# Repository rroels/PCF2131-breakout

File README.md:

# NXP PCF2131 RTC Breakout Board

> [!WARNING]
> The information and material (code, designs, files, ...) are provided "AS IS". We make no representation or warranty of any kind, express or implied, regarding the accuracy, adequacy, validity, reliability, availability, or completeness of any information or material. Use this at your own risk.

## Introduction

This repository contains a small breakout board for the NXP PCF2131 RTC.

The board has already been manufactured and tested, and I can confirm it works.

However, some design choices have been made that might not meet your needs. 
For instance, the board is wired for I2C communication only, and there is no support for battery switch-over.
Please read section "Design Considerations" for more info on the design choices.

For use with an Arduino, the [RTC NXP Arduino](https://reference.arduino.cc/reference/en/libraries/rtc_nxp_arduino/) library can be used to interface with the chip.

## Design Considerations

* Although the PCF2131 supports both I2C and SPI, they require different circuitry, and the choice was made to only support I2C.
* As expected for a I2C, pull-up resistors are present on the I2C lines.
* The board was not made to support battery switch-over, and for this reason, it does not have the suggested RC filter circuitry.

## Schematics

We base ourselves on the following recommended circuits from the datasheet:

I deliberately left out the RC filter for battery switch-over functionality, which led to the following schematics:

## Bill of Materials (BOM)

| Reference | Footprint                                   | Qty | Value      |
|-----------|---------------------------------------------|-----|------------|
| C1        | C_0603_1608Metric_Pad1.08x0.95mm_HandSolder | 1   | 1nF        |
| R3,R4     | R_0603_1608Metric_Pad0.98x0.95mm_HandSolder | 2   | 10k        |
| J1        | PinHeader_2x02_P2.54mm_Vertical             | 1   | Conn_01x04 |
| R2,R1     | R_0603_1608Metric_Pad0.98x0.95mm_HandSolder | 2   | 4.7k       |
| C2        | C_0603_1608Metric_Pad1.08x0.95mm_HandSolder | 1   | 100nF      |
| IC1       | SON50P350X450X150-17N-D                     | 1   | PCF2131TFY |
| J2        | PinHeader_1x07_P2.54mm_Horizontal           | 1   | Conn_01x07 |

See image of the PCB below to have a better idea of what these components look like. 

All capacitors and resistors and SMD 0603. Instead of the horizontal pin header I used, a vertical pin header will also work fine (as long as the pitch is 2.54mm).

## How to Obtain the Physical PCB

The Gerber file is in this repository (`gerber/PCF2131-breakout.zip`). Simply upload this file a PCB manufacturer of your choice (JLPCB, PCBWay, ...), and you they will make it for you for as low as \$5 for 5 pieces (with the cheapest shipping option, which can take a few weeks).

> [!WARNING]
> Note that you will still have to solder the components onto the PCB yourself!

## How to Edit Design

Everything you need to edit this design in KiCad 8 is included in the repository. 

However, this project uses symbols, footprints and 3D models from [Component Search Engine](https://componentsearchengine.com/). Their license allows us to do pretty much whatever we want with them, except redistributing them. For this reason I can't include them in this repository. 

If you would like to edit the design yourself, you will need to download the following component libraries from [https://componentsearchengine.com/](https://componentsearchengine.com/) (it's free!):

* [https://componentsearchengine.com/part-view/PCF2131TFY/NXP](https://componentsearchengine.com/part-view/PCF2131TFY/NXP)

From the downloaded zip file, move the content of the `KiCad` and `3D` subfolders into the project structure, so that the end-result looks like this:

The KiCad project is configured to look for these files in these locations, using relative paths, so no changes to the project itself are required. 

## Related Sources

* [https://www.nxp.com/products/analog-and-mixed-signal/real-time-clocks/nano-power-highly-accurate-rtc-with-integrated-quartz-crystal:PCF2131](https://www.nxp.com/products/analog-and-mixed-signal/real-time-clocks/nano-power-highly-accurate-rtc-with-integrated-quartz-crystal:PCF2131)

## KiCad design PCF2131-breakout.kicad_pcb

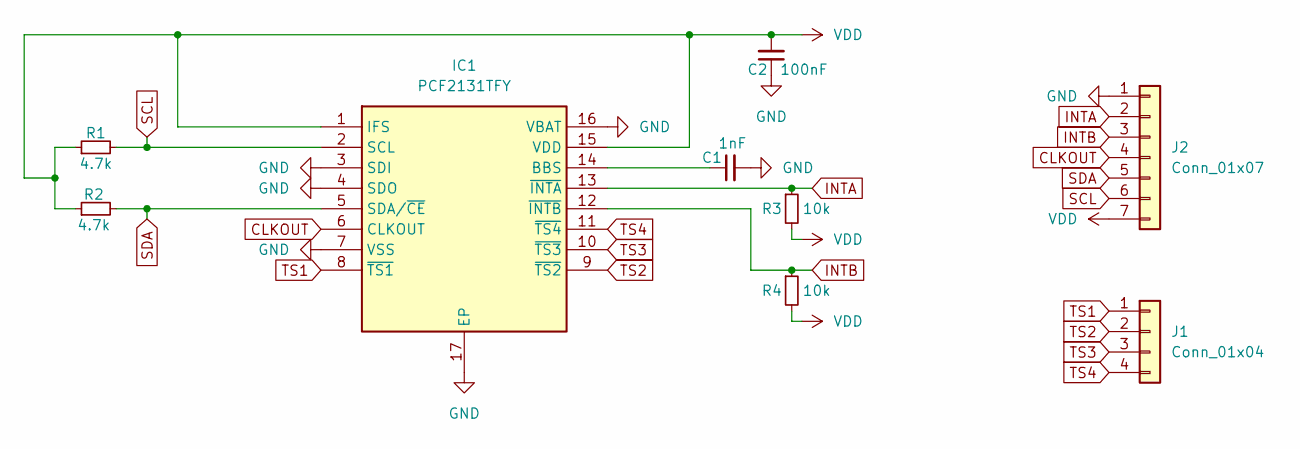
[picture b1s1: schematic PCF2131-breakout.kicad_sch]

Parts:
C1: 1nF; C_0603_1608Metric_Pad1.08x0.95mm_HandSolder
C2: 100nF; C_0603_1608Metric_Pad1.08x0.95mm_HandSolder
IC1: PCF2131TFY; SON50P350X450X150-17N-D; Manufacturer_Part_Number PCF2131TFY; Mouser Part Number 771-PCF2131TFY
J1: Conn_01x04; PinHeader_2x02_P2.54mm_Vertical
J2: Conn_01x07; PinHeader_1x07_P2.54mm_Horizontal
R1, R2: 4.7k; R_0603_1608Metric_Pad0.98x0.95mm_HandSolder
R3, R4: 10k; R_0603_1608Metric_Pad0.98x0.95mm_HandSolder

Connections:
CLKOUT: IC1.6 (CLKOUT), J2.4
GND: C1.2, C2.1, IC1.3 (SDI), IC1.4 (SDO), IC1.7 (VSS), IC1.16 (VBAT), IC1.17 (EP), J2.1
INTA: IC1.13 (~INTA), J2.2, R3.1
INTB: IC1.12 (~INTB), J2.3, R4.1
unnamed: C1.1, IC1.14 (BBS)
SCL: IC1.2 (SCL), J2.6, R1.2
SDA: IC1.5 (SDA/~CE), J2.5, R2.2
TS1: IC1.8 (~TS1), J1.1
TS2: IC1.9 (~TS2), J1.2
TS3: IC1.10 (~TS3), J1.3
TS4: IC1.11 (~TS4), J1.4
VDD: C2.2, IC1.1 (IFS), IC1.15 (VDD), J2.7, R1.1, R2.1, R3.2, R4.2

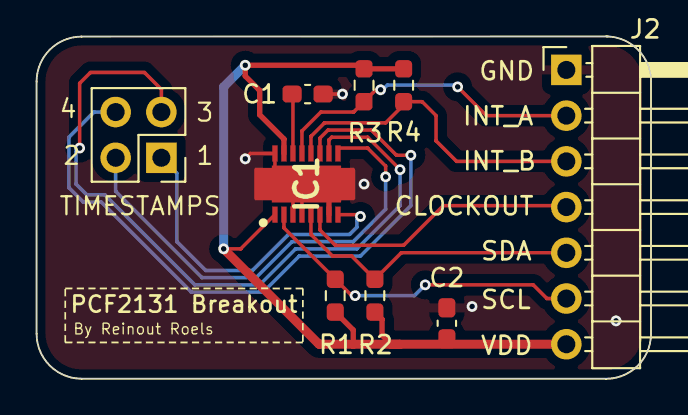
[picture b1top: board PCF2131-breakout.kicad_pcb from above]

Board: 2 copper layers, 34.2 x 19.0 mm, 9 parts (0 on the bottom side), 12 nets.

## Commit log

2024-08-02 add gitignore
2024-08-02 add datasheets
2024-08-02 add gerber files
2024-08-02 add kicad files
2024-08-02 update gitignore
